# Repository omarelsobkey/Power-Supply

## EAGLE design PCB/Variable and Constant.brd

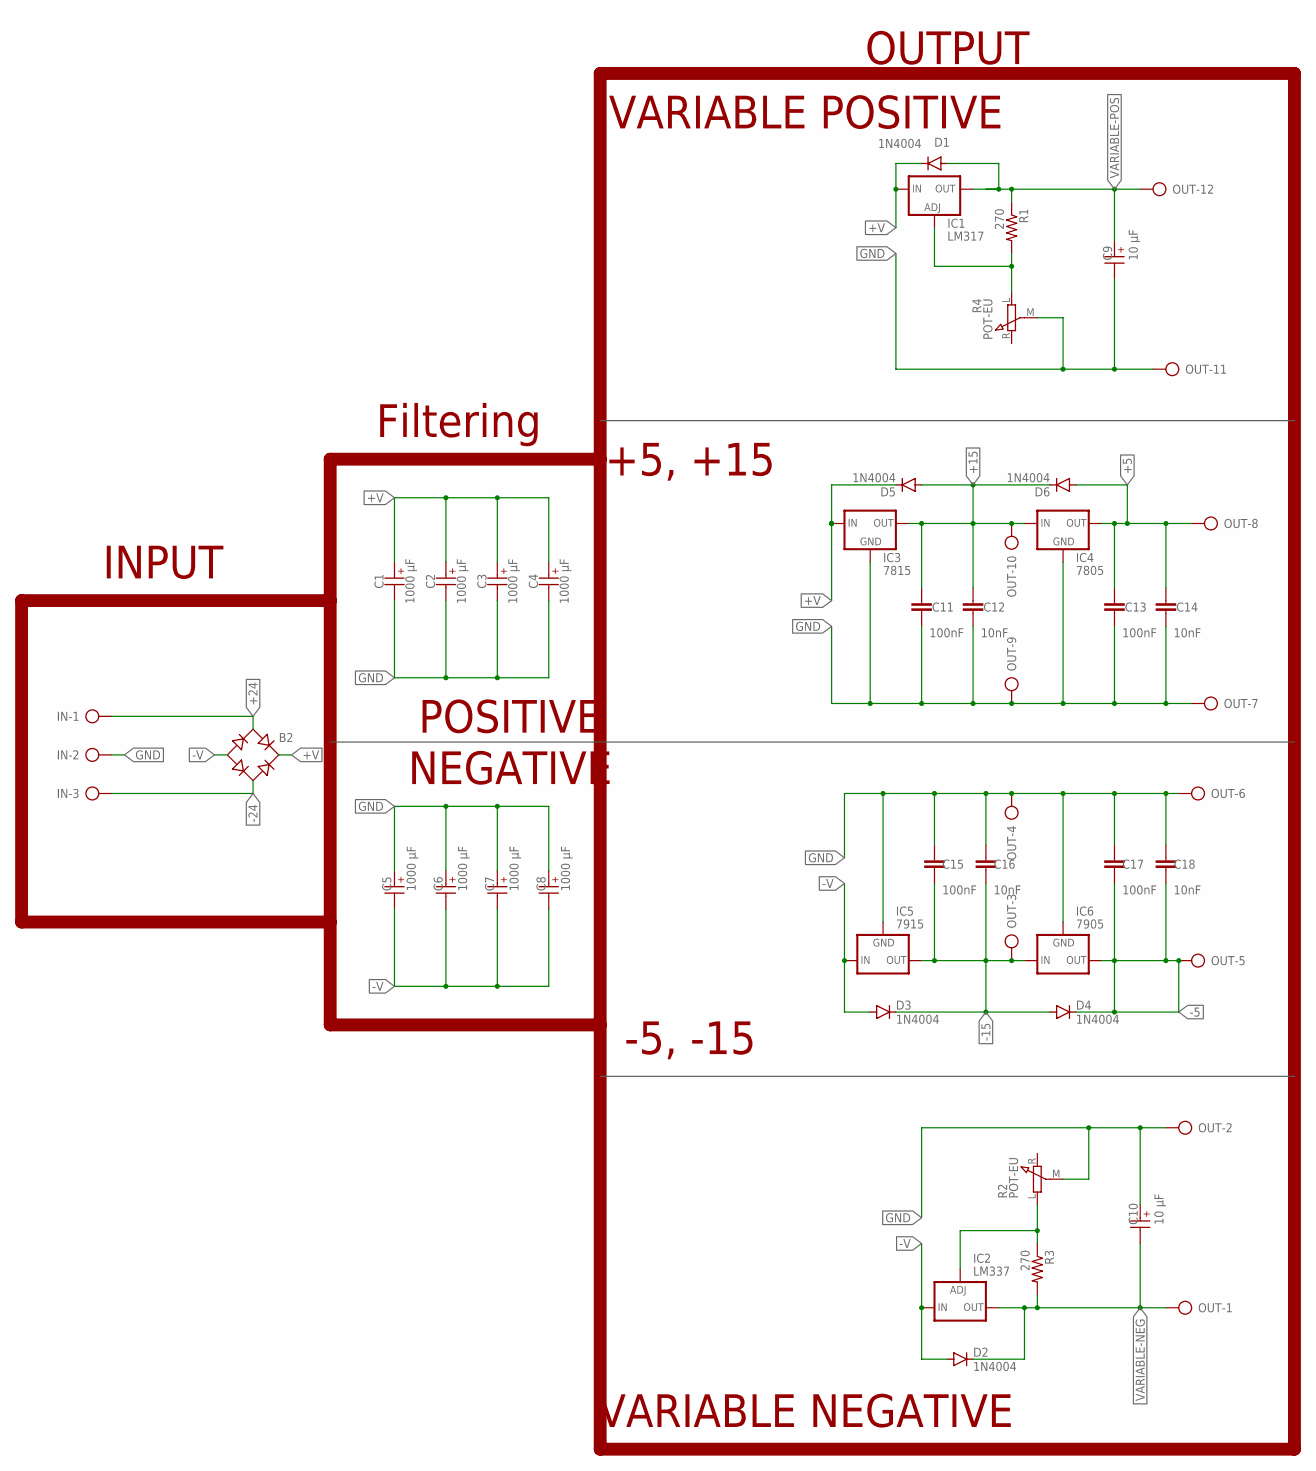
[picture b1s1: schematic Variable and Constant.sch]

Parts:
B2: RB1A
C1, C2, C3, C4, C5, C6, C7, C8: 1000 µF; WCAP-ATG8_10X12.5(DXL)
C9, C10: 10 µF; WCAP-ATG8_5X11(DXL)
C11, C13, C15, C17: 100nF; CAP-PTH-SMALL-KIT
C12, C14, C16, C18: 10nF; CAP-PTH-SMALL-KIT
D1, D2, D3, D4, D5, D6: 1N4004; DO41-10
IC1: LM317; 317TS
IC2: LM337; 337TS
IC3: 7815; 78XXS
IC4: 7805; 78XXS
IC5: 7915; 79XXS
IC6: 7905; 79XXS
IN: AK500/3-H
OUT: AK500/12-H
R1, R3: 270; AXIAL-0.3
R2, R4: POT-EU; RM-065

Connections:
+5: C13.1, C14.1, D6.A, IC4.OUT, OUT.8
+15: C11.1, C12.1, D5.A, D6.C, IC3.OUT, IC4.IN, OUT.10
+24: B2.AC1, IN.1
+V: B2.+, C1.1 (+), C2.1 (+), C3.1 (+), C4.1 (+), D1.C, D5.C, IC1.3 (IN), IC3.IN
-5: C17.2, C18.2, D4.C, IC6.OUT, OUT.5
-15: C15.2, C16.2, D3.C, D4.A, IC5.OUT, IC6.IN, OUT.3
-24: B2.AC2, IN.3
-V: B2.-, C5.2 (-), C6.2 (-), C7.2 (-), C8.2 (-), D2.A, D3.A, IC2.2 (IN), IC5.IN
GND: C1.2 (-), C2.2 (-), C3.2 (-), C4.2 (-), C5.1 (+), C6.1 (+), C7.1 (+), C8.1 (+), C9.2 (-), C10.1 (+), C11.2, C12.2, C13.2, C14.2, C15.1, C16.1, C17.1, C18.1, IC3.GND, IC4.GND, IC5.GND, IC6.GND, IN.2, OUT.2, OUT.4, OUT.6, OUT.7, OUT.9, OUT.11, R2.M, R4.M
unnamed: IC2.1 (ADJ), R2.L, R3.P$1 (1)
unnamed: IC1.1 (ADJ), R1.P$2 (2), R4.L
VARIABLE-NEG: C10.2 (-), D2.C, IC2.3 (OUT), OUT.1, R3.P$2 (2)
VARIABLE-POS: C9.1 (+), D1.A, IC1.2 (OUT), OUT.12, R1.P$1 (1)

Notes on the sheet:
INPUT
Filtering
OUTPUT
VARIABLE POSITIVE
+5, +15
-5, -15
VARIABLE NEGATIVE
POSITIVE
NEGATIVE

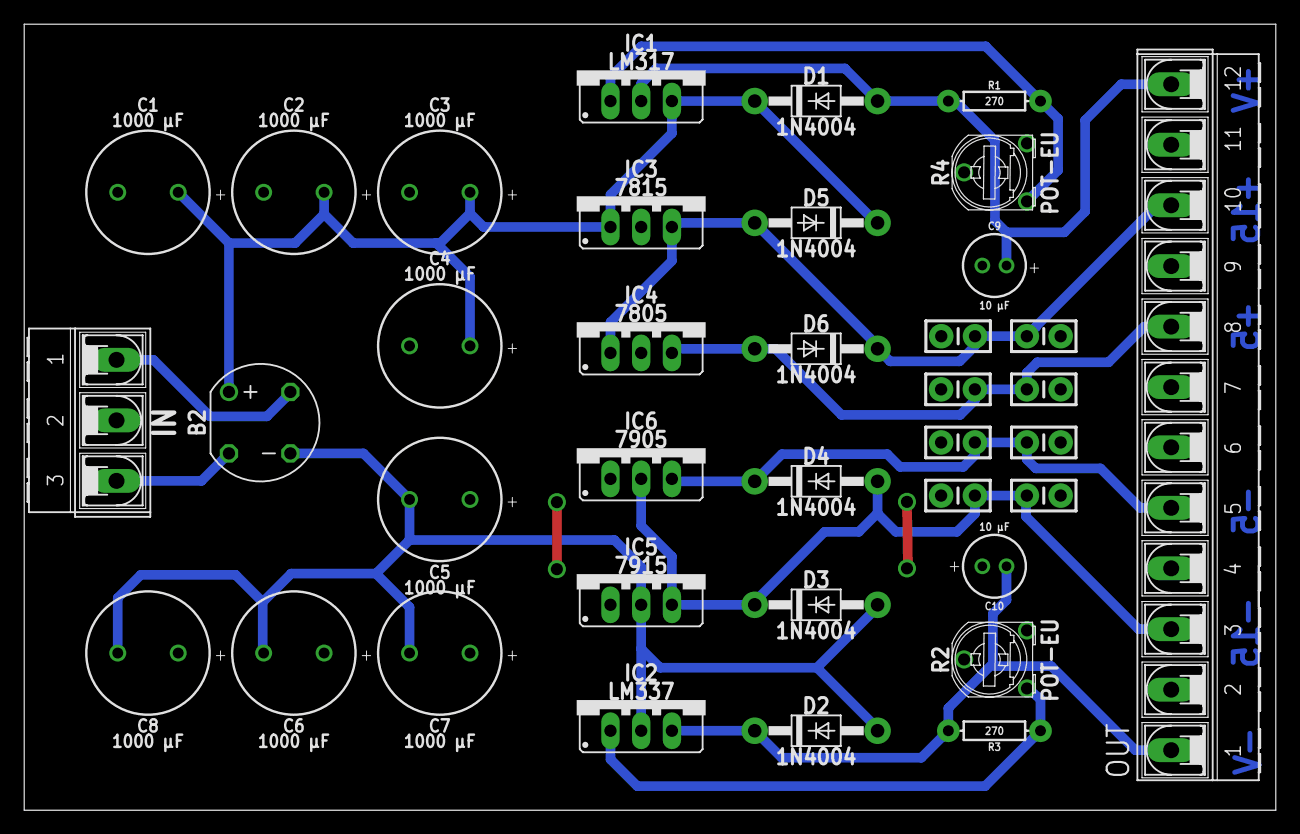
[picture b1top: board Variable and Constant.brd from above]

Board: 2 copper layers, 103.5 x 65.0 mm, 37 parts (0 on the bottom side), 13 nets.

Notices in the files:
parts and their libraries:
Aluminium Electrolyt Capacitors: Copyright: Würth Elektronik
SparkFun-Capacitors: Licensing: Creative Commons ShareAlike 4.0 International - https://creativecommons.org/licenses/by-sa/4.0
